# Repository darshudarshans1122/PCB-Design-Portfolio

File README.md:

# PCB-Design-Portfolio
PCB design projects created using KiCad

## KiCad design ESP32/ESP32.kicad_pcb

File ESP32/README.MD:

# ESP32 Development Board PCB

## 📌 Overview

This project is a custom PCB design based on the ESP32-WROOM-32 module.
The board provides easy access to ESP32 GPIO pins and includes USB connectivity,
power regulation, and programming/reset controls.

## 🔧 Features

- ESP32-WROOM-32 module
- 32 GPIO pins (16 pins on each side)
- USB interface for programming and power
- 3.3V voltage regulation
- EN/Reset button
- BOOT button
- Status/Power LED
- GPIO breakout headers
- Decoupling capacitors for stable operation

## 🛠️ Tools Used

- KiCad
- Schematic Capture
- PCB Layout
- 3D Viewer

## 📐 PCB Design

- PCB designed using KiCad
- Two-layer PCB
- Through-hole pin headers for GPIO access
- Ground plane implemented for improved signal integrity and power distribution

## 🎯 Learning Objectives

This project helped me practice:

- ESP32 schematic design
- Component selection and footprint assignment
- Two-layer PCB routing
- Ground plane/pour implementation
- Design Rule Checking (DRC)
- PCB layout and component placement
- 3D visualization in KiCad

## 📷 Project Preview

ESP32-based custom development board designed from schematic to PCB layout.

## 👨‍💻 Author

**Darshan**

Electronics & Communication Engineering  
PCB Design | Embedded Systems | KiCad

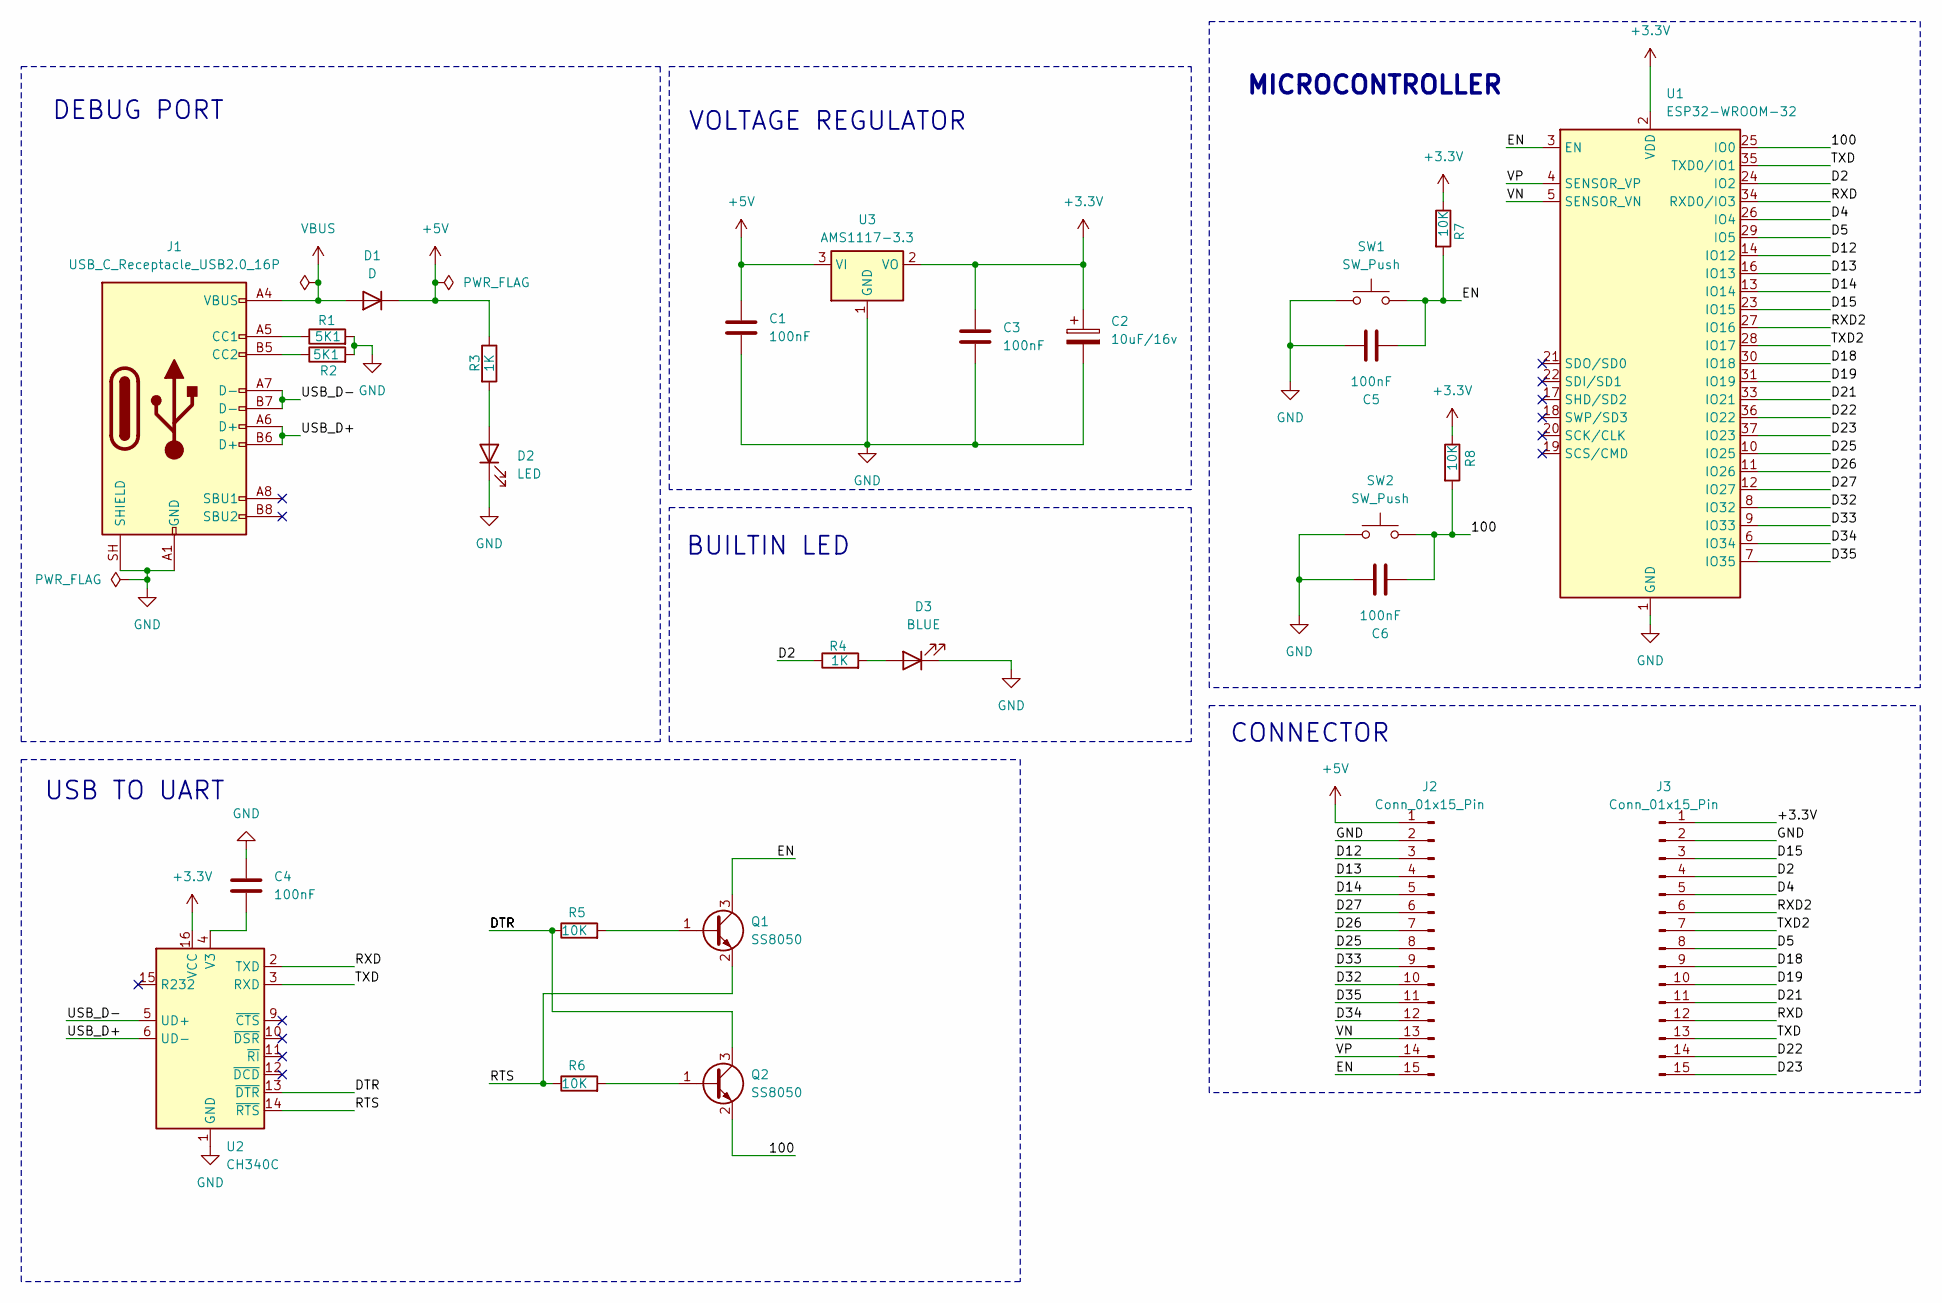
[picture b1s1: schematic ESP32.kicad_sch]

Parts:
C1, C3, C4, C5, C6: 100nF; C_0603_1608Metric
C2: 10uF/16v; CP_EIA-3216-12_Kemet-S
D1: D; D_0603_1608Metric
D2: LED; LED_0603_1608Metric
D3: BLUE; LED_0603_1608Metric
J1: USB_C_Receptacle_USB2.0_16P; USB_C_Receptacle_HRO_TYPE-C-31-M-12
J2, J3: Conn_01x15_Pin; PinHeader_1x15_P2.54mm_Vertical
Q1, Q2: SS8050; SOT-23
R1, R2: 5K1; R_0603_1608Metric
R3, R4: 1K; R_0603_1608Metric
R5, R6, R7, R8: 10K; R_0603_1608Metric
SW1, SW2: SW_Push; SW_Push_SPST_NO_Alps_SKRK
U1: ESP32-WROOM-32
U2: CH340C; SOIC-16_3.9x9.9mm_P1.27mm
U3: AMS1117-3.3; SOT-223-3_TabPin2

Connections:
+3.3V: C2.1, C3.1, J3.1, R7.1, R8.1, U1.2 (VDD), U2.16 (VCC), U3.2 (VO)
+5V: C1.1, D1.1 (K), J2.1, R3.1, U3.3 (VI)
/100: C6.1, Q2.2 (E), R8.2, SW2.2, U1.25 (IO0)
/D2: J3.4, R4.1, U1.24 (IO2)
/D4: J3.5, U1.26 (IO4)
/D5: J3.8, U1.29 (IO5)
/D12: J2.3, U1.14 (IO12)
/D13: J2.4, U1.16 (IO13)
/D14: J2.5, U1.13 (IO14)
/D15: J3.3, U1.23 (IO15)
/D18: J3.9, U1.30 (IO18)
/D19: J3.10, U1.31 (IO19)
/D21: J3.11, U1.33 (IO21)
/D22: J3.14, U1.36 (IO22)
/D23: J3.15, U1.37 (IO23)
/D25: J2.8, U1.10 (IO25)
/D26: J2.7, U1.11 (IO26)
/D27: J2.6, U1.12 (IO27)
/D32: J2.10, U1.8 (IO32)
/D33: J2.9, U1.9 (IO33)
/D34: J2.12, U1.6 (IO34)
/D35: J2.11, U1.7 (IO35)
/DTR: Q2.3 (C), R5.1, U2.13 (~DTR)
/EN: C5.1, J2.15, Q1.3 (C), R7.2, SW1.2, U1.3 (EN)
/RTS: Q1.2 (E), R6.1, U2.14 (~RTS)
/RXD: J3.12, U1.34 (RXD0/IO3), U2.2 (TXD)
/RXD2: J3.6, U1.27 (IO16)
/TXD: J3.13, U1.35 (TXD0/IO1), U2.3 (RXD)
/TXD2: J3.7, U1.28 (IO17)
/USB_D+: J1.A6 (D+), J1.B6 (D+), U2.6 (UD-)
/USB_D-: J1.A7 (D-), J1.B7 (D-), U2.5 (UD+)
/VN: J2.13, U1.5 (SENSOR_VN)
/VP: J2.14, U1.4 (SENSOR_VP)
GND: C1.2, C2.2, C3.2, C4.1, C5.2, C6.2, D2.1 (K), D3.1 (K), J1.A1 (GND), J1.A12 (GND), J1.B1 (GND), J1.B12 (GND), J1.SH (SHIELD), J2.2, J3.2, R1.2, R2.2, SW1.1, SW2.1, U1.1 (GND), U1.15 (GND), U1.38 (GND), U1.39 (GND), U2.1 (GND), U3.1 (GND)
unnamed: D2.2 (A), R3.2
unnamed: D3.2 (A), R4.2
unnamed: J1.A5 (CC1), R1.1
unnamed: J1.B5 (CC2), R2.1
unnamed: Q1.1 (B), R5.2
unnamed: Q2.1 (B), R6.2
unnamed: C4.2, U2.4 (V3)
VBUS: D1.2 (A), J1.A4 (VBUS), J1.A9 (VBUS), J1.B4 (VBUS), J1.B9 (VBUS)

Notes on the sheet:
MICROCONTROLLER
VOLTAGE REGULATOR
DEBUG PORT
USB TO UART
CONNECTOR
BUILTIN LED

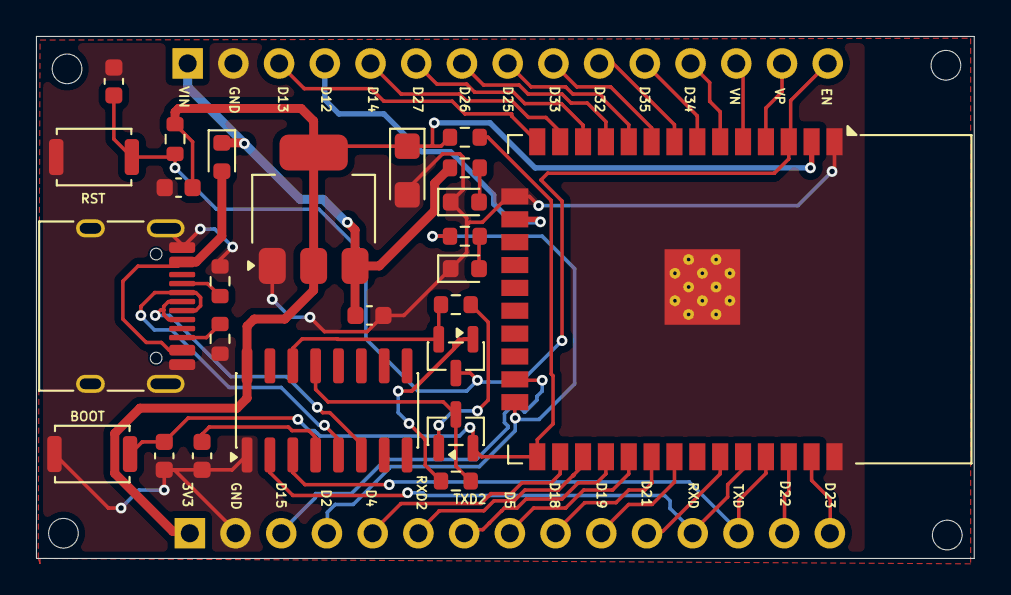
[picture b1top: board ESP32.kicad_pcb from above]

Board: 2 copper layers, 52.1 x 29.0 mm, 27 parts (0 on the bottom side), 42 nets.

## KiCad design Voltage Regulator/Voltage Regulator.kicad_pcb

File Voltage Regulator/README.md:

🔋 Voltage Regulator PCB

A compact voltage regulator PCB designed to convert a higher DC input voltage into a stable regulated DC output. This project focuses on schematic design, component selection, PCB placement, and routing using KiCad.

⚙️ Features

- Stable regulated DC output
- Input and output filtering
- LED power indicator
- Compact PCB design
- Proper power and ground routing

🔧 Main Components

- Voltage regulator IC
- Input capacitor
- Output capacitor
- LED
- Current-limiting resistor
- Input/Output connectors

🛠️ Design Process

1. Designed the schematic in KiCad
2. Selected and assigned footprints
3. Created the PCB layout
4. Placed components
5. Routed power and ground connections
6. Completed PCB layout and DRC checks

🎯 Learning Outcomes

- Voltage regulator circuit design
- Power PCB layout
- Component placement
- Power and ground routing
- KiCad schematic-to-PCB workflow

🛠️ Tools Used

KiCad | PCB Design | Electronics

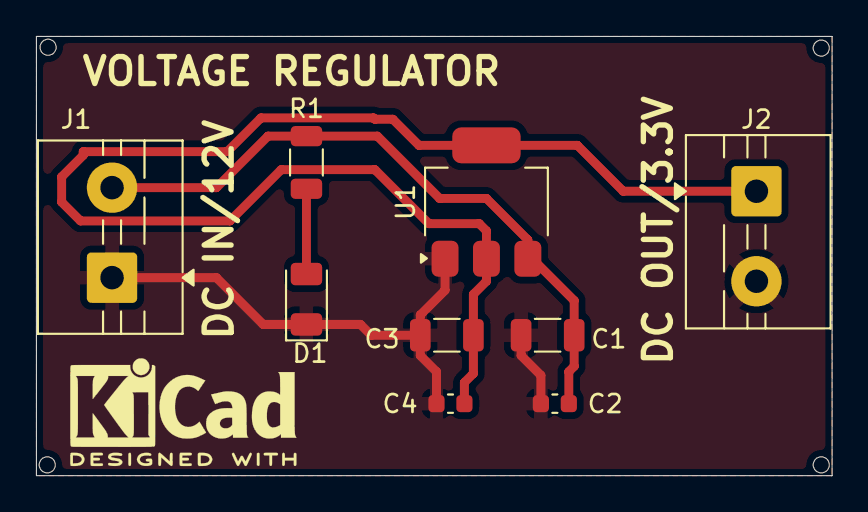
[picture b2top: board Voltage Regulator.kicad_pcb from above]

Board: 2 copper layers, 44.2 x 24.4 mm, 9 parts (0 on the bottom side), 4 nets.

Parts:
C1, C3: 10uF; C_1206_3216Metric
C2, C4: 0.1uF; C_0603_1608Metric
D1: LED; LED_1206_3216Metric
J1, J2: Screw_Terminal_01x02; TerminalBlock_MaiXu_MX126-5.0-02P_1x02_P5.00mm
R1: 2.2k; R_1206_3216Metric
U1: AMS1117-3.3; SOT-223-3_TabPin2

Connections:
/IN_12V: C1.1, C2.1, J1.2, R1.1, U1.3 (VI)
/OUT_3.3V: C3.1, C4.1, J2.1, U1.2 (VO)
GND: C1.2, C2.2, C3.2, C4.2, D1.1 (K), J1.1, J2.2, U1.1 (GND)
unnamed: D1.2 (A), R1.2

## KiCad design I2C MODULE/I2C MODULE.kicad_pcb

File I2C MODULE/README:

I²C LCD Backpack PCB

A compact I²C LCD Backpack PCB designed to interface a 16×2 LCD with a microcontroller using the I²C protocol.

Features

- PCF8574 I²C I/O Expander
- 16×2 LCD interface
- Contrast adjustment
- Backlight control
- Compact PCB design
- Designed using KiCad

Tools

- KiCad
- PCB Design & Layout
- Schematic Capture
- ERC/DRC Verification

Applications

Arduino, Raspberry Pi, embedded systems, and IoT projects.

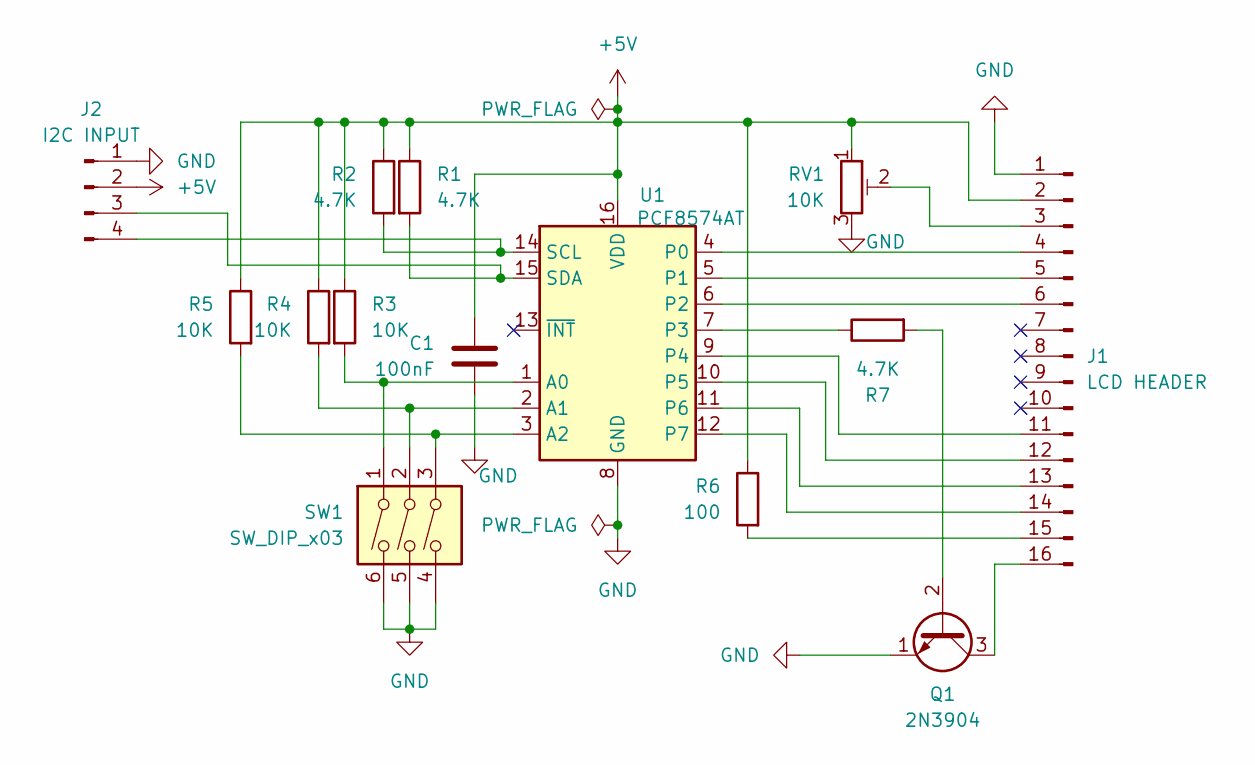
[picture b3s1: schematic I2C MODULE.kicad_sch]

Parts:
C1: 100nF; C_0201_0603Metric
J1: LCD HEADER; PinHeader_1x16_P2.54mm_Vertical
J2: I2C INPUT; PinHeader_1x04_P2.54mm_Horizontal
Q1: 2N3904; TO-92_Inline
R1, R2, R7: 4.7K; R_0201_0603Metric
R3, R4, R5: 10K; R_0201_0603Metric
R6: 100; R_0201_0603Metric
RV1: 10K; Potentiometer_Bourns_3296W_Vertical
SW1: SW_DIP_x03; DIP-6_W7.62mm
U1: PCF8574AT; SOIC-16W_7.5x10.3mm_P1.27mm

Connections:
+5V: C1.1, J1.2, J2.2, R1.1, R2.1, R3.1, R4.1, R5.1, R6.1, RV1.1, U1.16 (VDD)
GND: C1.2, J1.1, J2.1, Q1.1 (E), RV1.3, SW1.4, SW1.5, SW1.6, U1.8 (GND)
unnamed: J1.3, RV1.2
unnamed: J1.4, U1.4 (P0)
unnamed: J1.5, U1.5 (P1)
unnamed: J1.6, U1.6 (P2)
unnamed: J1.11, U1.9 (P4)
unnamed: J1.12, U1.10 (P5)
unnamed: J1.13, U1.11 (P6)
unnamed: J1.14, U1.12 (P7)
unnamed: J1.15, R6.2
unnamed: J1.16, Q1.3 (C)
unnamed: J2.3, R1.2, U1.15 (SDA)
unnamed: J2.4, R2.2, U1.14 (SCL)
unnamed: Q1.2 (B), R7.2
unnamed: R3.2, SW1.1, U1.1 (A0)
unnamed: R4.2, SW1.2, U1.2 (A1)
unnamed: R5.2, SW1.3, U1.3 (A2)
unnamed: R7.1, U1.7 (P3)

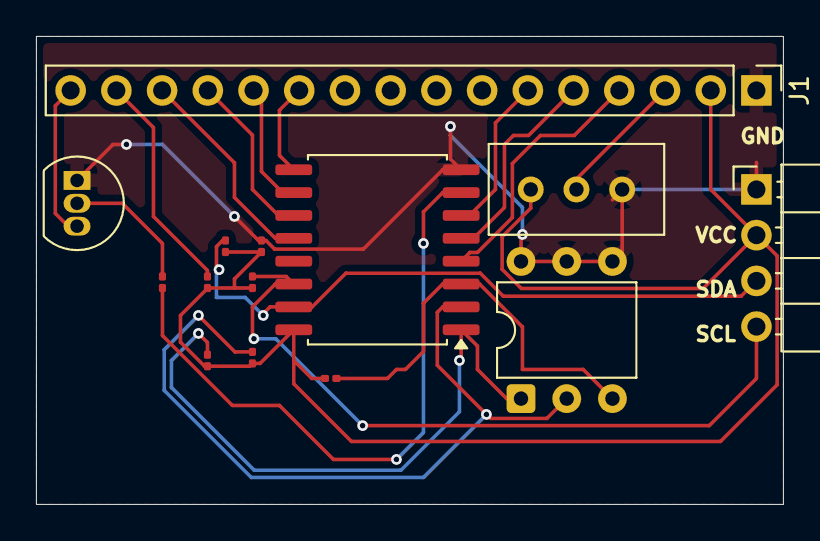
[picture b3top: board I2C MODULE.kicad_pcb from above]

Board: 2 copper layers, 41.5 x 26.0 mm, 14 parts (0 on the bottom side), 19 nets.

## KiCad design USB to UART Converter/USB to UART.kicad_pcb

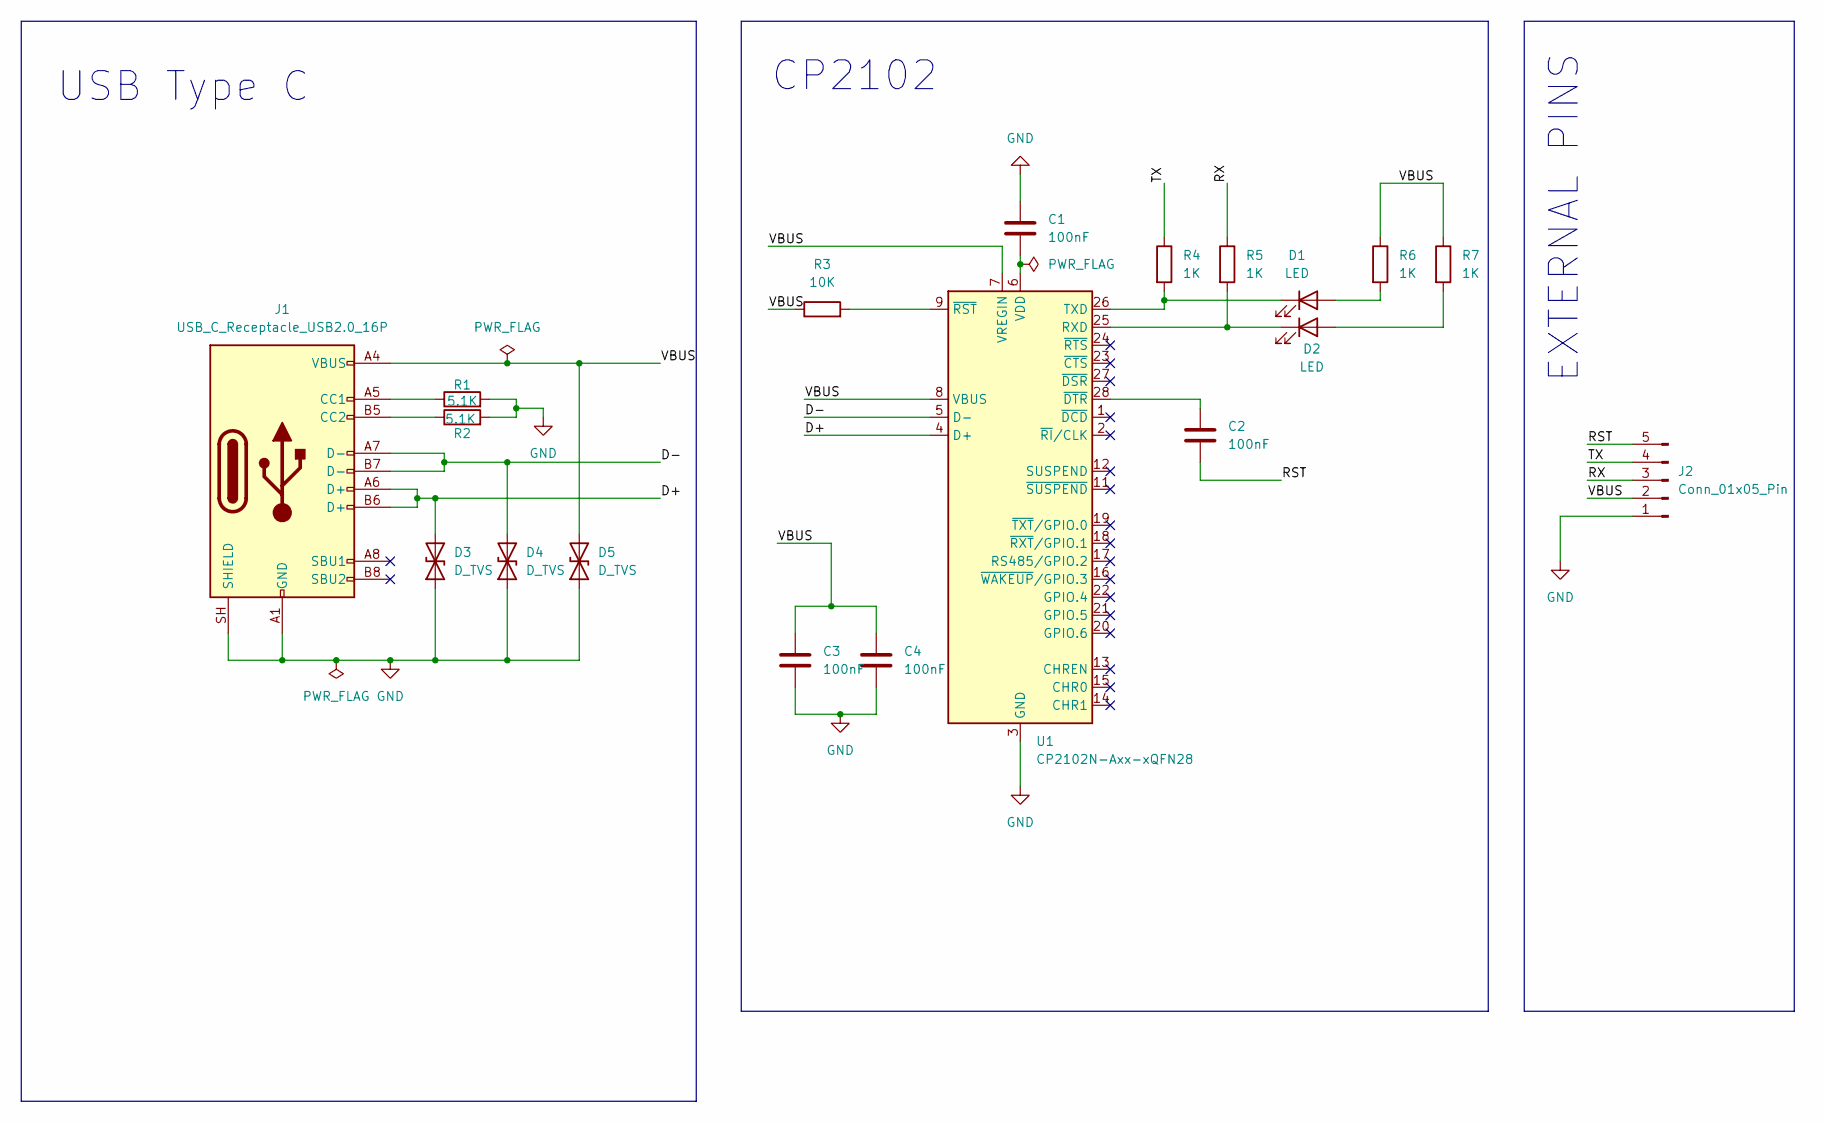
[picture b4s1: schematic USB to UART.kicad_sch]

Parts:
C1, C2, C3, C4: 100nF; C_0201_0603Metric
D1, D2: LED; LED_0201_0603Metric
D3, D4, D5: D_TVS; D_SOD-323
J1: USB_C_Receptacle_USB2.0_16P; USB_C_Receptacle_HRO_TYPE-C-31-M-12
J2: Conn_01x05_Pin; PinHeader_1x05_P2.54mm_Horizontal
R1, R2: 5.1K; R_0201_0603Metric
R3: 10K; R_0201_0603Metric
R4, R5, R6, R7: 1K; R_0201_0603Metric
U1: CP2102N-Axx-xQFN28; QFN-28-1EP_5x5mm_P0.5mm_EP3.35x3.35mm

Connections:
/D+: D3.2 (A2), J1.A6 (D+), J1.B6 (D+), U1.4 (D+)
/D-: D4.2 (A2), J1.A7 (D-), J1.B7 (D-), U1.5 (D-)
/RST: C2.2, J2.5
/RX: J2.3, R5.1
/TX: J2.4, R4.1
/VBUS: C3.1, C4.1, D5.2 (A2), J1.A4 (VBUS), J1.A9 (VBUS), J1.B4 (VBUS), J1.B9 (VBUS), J2.2, R3.1, R6.1, R7.1, U1.7 (VREGIN), U1.8 (VBUS)
GND: C1.1, C3.2, C4.2, D3.1 (A1), D4.1 (A1), D5.1 (A1), J1.A1 (GND), J1.A12 (GND), J1.B1 (GND), J1.B12 (GND), J1.SH (SHIELD), J2.1, R1.2, R2.2, U1.3 (GND), U1.29 (GND)
unnamed: D1.2 (A), R6.2
unnamed: D1.1 (K), R4.2, U1.26 (TXD)
unnamed: D2.2 (A), R7.2
unnamed: D2.1 (K), R5.2, U1.25 (RXD)
unnamed: J1.A5 (CC1), R1.1
unnamed: J1.B5 (CC2), R2.1
unnamed: C1.2, U1.6 (VDD)
unnamed: C2.1, U1.28 (~DTR)
unnamed: R3.2, U1.9 (~RST)

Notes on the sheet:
CP2102
USB Type C
EXTERNAL PINS

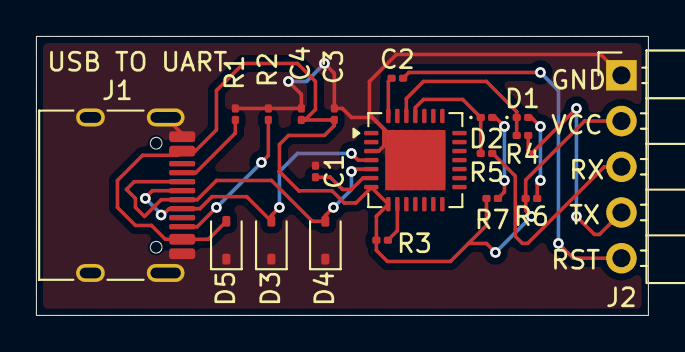
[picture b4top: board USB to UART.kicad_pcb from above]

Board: 2 copper layers, 34.0 x 15.5 mm, 19 parts (0 on the bottom side), 16 nets.

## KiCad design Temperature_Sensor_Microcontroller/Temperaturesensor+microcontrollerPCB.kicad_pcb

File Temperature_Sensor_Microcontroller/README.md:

# Temperature Sensor Microcontroller PCB

## Project Overview
A temperature sensing and monitoring PCB designed using KiCad.

## Design Process
- Schematic design
- Component selection
- PCB layout
- PCB routing
- Design Rule Check (DRC)
- 3D PCB visualization

## Tools Used
- KiCad
- PCB Design and Layout

## Project Files
The complete KiCad design files and project documentation are included in this folder.

## Results
- Successfully routed PCB
- DRC verification completed
- 3D PCB model generated

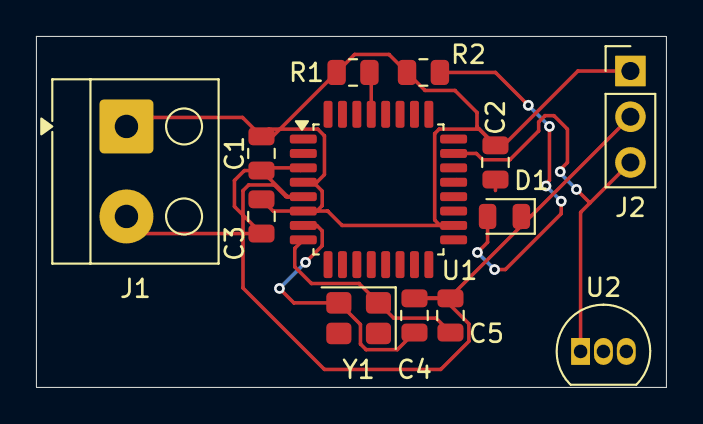
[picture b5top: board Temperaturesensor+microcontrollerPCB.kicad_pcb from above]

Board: 2 copper layers, 35.0 x 19.5 mm, 13 parts (0 on the bottom side), 7 nets.

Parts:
C1, C2: 100nF; C_0805_2012Metric
C3: 10uF; C_0805_2012Metric
C4, C5: 22pF; C_0805_2012Metric
D1: LED; LED_0805_2012Metric
J1: Conn_01x02_Pin; Altech_AK100_1x02_P5.00mm
J2: Conn_01x03_Pin; PinHeader_1x03_P2.54mm_Vertical
R1: 10k; R_0805_2012Metric
R2: 1k; R_0805_2012Metric
U1: ATmega328P-A; LQFP-32_7x7mm_P0.8mm
U2: LM35-D; TO-92_Inline
Y1: 16MHz; Crystal_SMD_3225-4Pin_3.2x2.5mm

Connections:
unnamed: D1.2 (A), R2.2
unnamed: C1.2, C2.2, C3.2, C4.2, C5.2, D1.1 (K), J1.2, J2.2, U1.3 (GND), U1.5 (GND), U1.21 (GND)
unnamed: C1.1, C2.1, C3.1, J1.1, J2.1, R1.2, R2.1, U1.4 (VCC), U1.6 (VCC), U1.18 (AVCC)
unnamed: J2.3, U1.23 (PC0), U2.1 (V_{OUT}_1)
unnamed: C4.1, U1.7 (XTAL1/PB6), Y1.2
unnamed: C5.1, U1.8 (XTAL2/PB7), Y1.1
unnamed: R1.1, U1.29 (~RESET/PC6)
